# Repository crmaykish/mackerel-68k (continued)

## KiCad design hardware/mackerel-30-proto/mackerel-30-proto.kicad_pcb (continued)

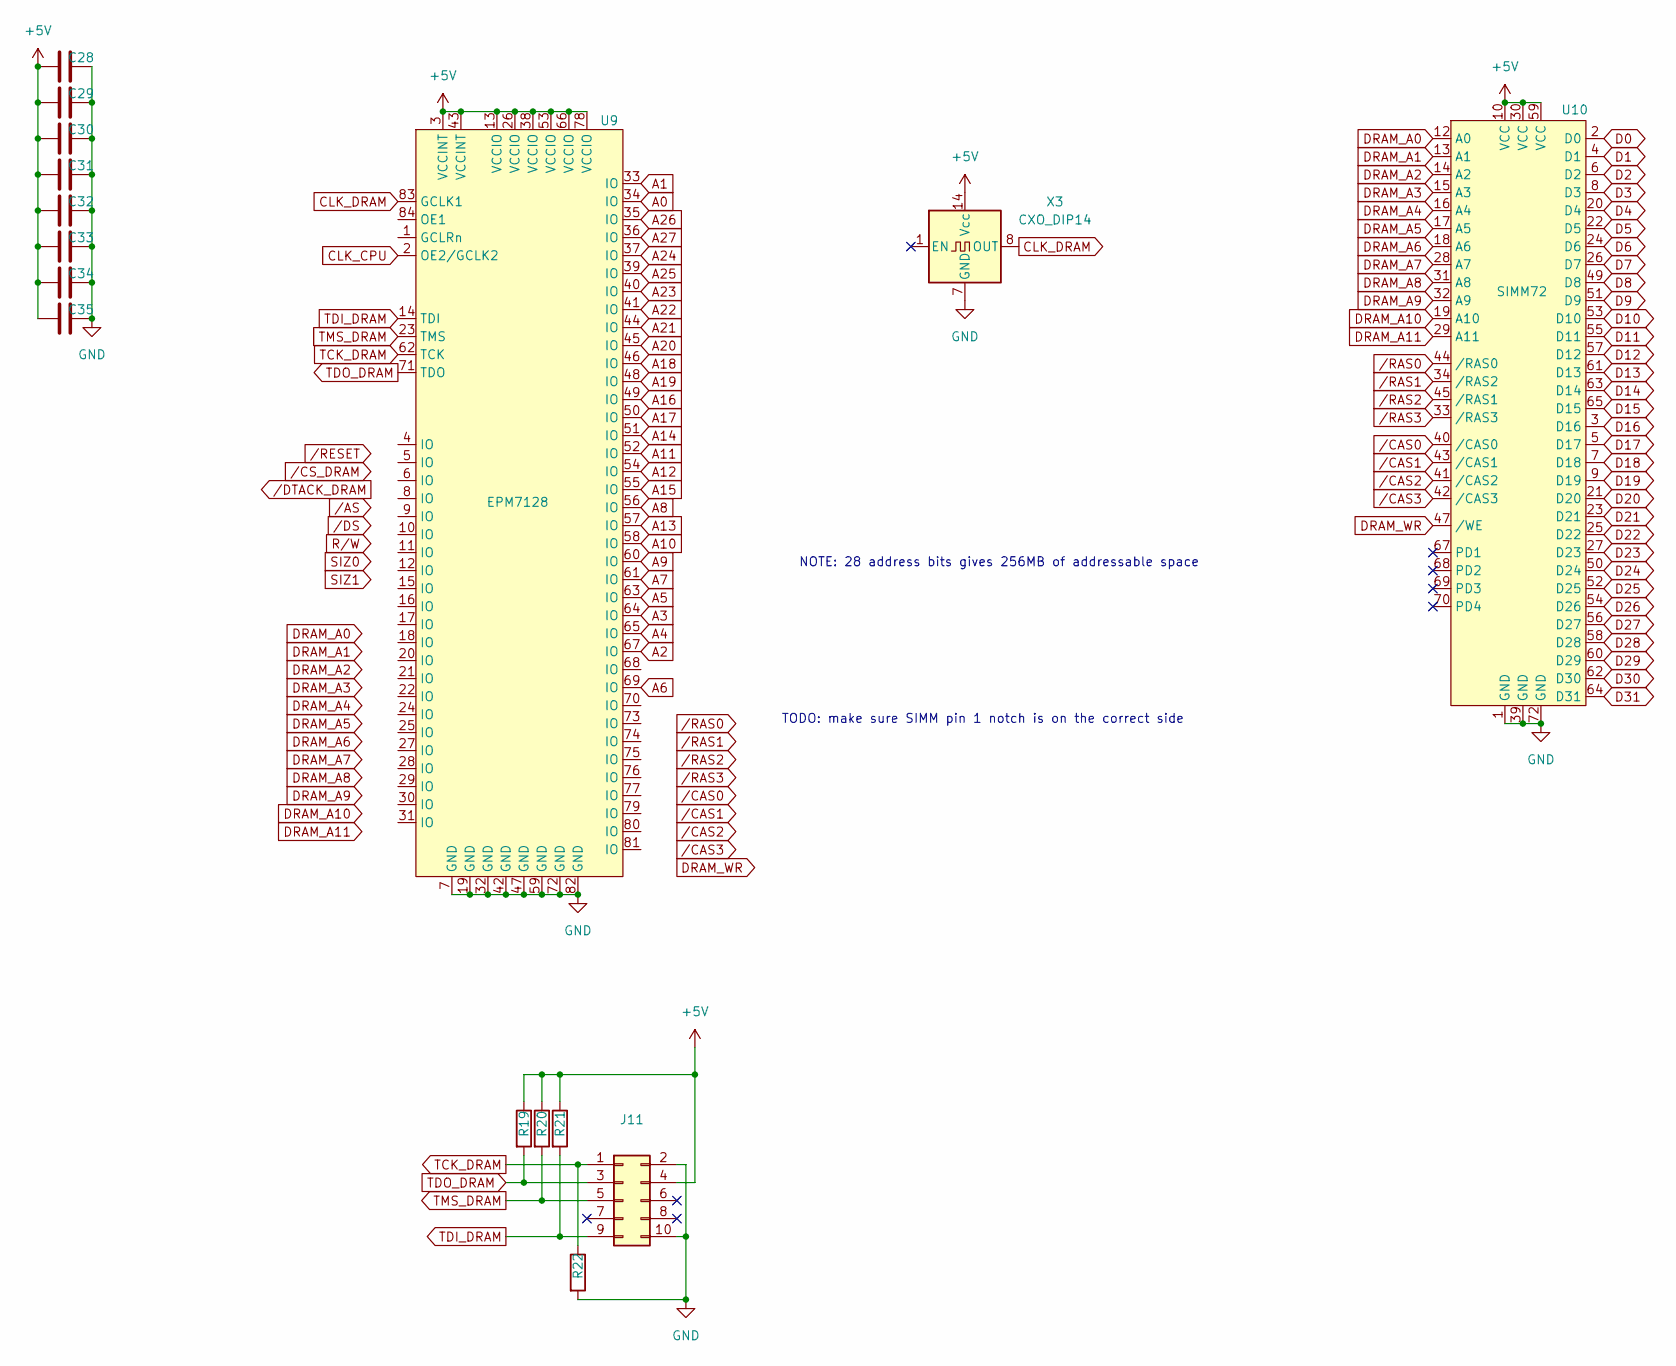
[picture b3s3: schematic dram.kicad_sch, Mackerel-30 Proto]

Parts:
C28, C29, C30, C31, C32, C33, C34, C35: 0.1uF; C_Disc_D4.3mm_W1.9mm_P5.00mm
J11: Conn_02x05_Odd_Even; IDC-Header_2x05_P2.54mm_Vertical
R19, R20, R21, R22: R; R_Axial_DIN0207_L6.3mm_D2.5mm_P7.62mm_Horizontal
U9: EPM7128; PLCC-84_THT-Socket
U10: SIMM72; SIMM-72
X3: CXO_DIP14; Oscillator_DIP-14

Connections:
+5V: C28.1, C29.1, C30.1, C31.1, C32.1, C33.1, C34.1, C35.1, J11.4, R19.1, R20.1, R21.1, U9.3 (VCCINT), U9.13 (VCCIO), U9.26 (VCCIO), U9.38 (VCCIO), U9.43 (VCCINT), U9.53 (VCCIO), U9.66 (VCCIO), U9.78 (VCCIO), U10.10 (VCC), U10.30 (VCC), U10.59 (VCC), X3.14 (Vcc); also elsewhere on the board
A0: U9.34 (IO); also elsewhere on the board
A1: U9.33 (IO); also elsewhere on the board
A2: U9.67 (IO); also elsewhere on the board
A3: U9.64 (IO); also elsewhere on the board
A4: U9.65 (IO); also elsewhere on the board
A5: U9.63 (IO); also elsewhere on the board
A6: U9.69 (IO); also elsewhere on the board
A7: U9.61 (IO); also elsewhere on the board
A8: U9.56 (IO); also elsewhere on the board
A9: U9.60 (IO); also elsewhere on the board
A10: U9.58 (IO); also elsewhere on the board
A11: U9.52 (IO); also elsewhere on the board
A12: U9.54 (IO); also elsewhere on the board
A13: U9.57 (IO); also elsewhere on the board
A14: U9.51 (IO); also elsewhere on the board
A15: U9.55 (IO); also elsewhere on the board
A16: U9.49 (IO); also elsewhere on the board
A17: U9.50 (IO); also elsewhere on the board
A18: U9.46 (IO); also elsewhere on the board
A19: U9.48 (IO); also elsewhere on the board
A20: U9.45 (IO); also elsewhere on the board
A21: U9.44 (IO); also elsewhere on the board
A22: U9.41 (IO); also elsewhere on the board
A23: U9.40 (IO); also elsewhere on the board
A24: U9.37 (IO); also elsewhere on the board
A25: U9.39 (IO); also elsewhere on the board
A26: U9.35 (IO); also elsewhere on the board
A27: U9.36 (IO); also elsewhere on the board
CLK_CPU: U9.2 (OE2/GCLK2); also elsewhere on the board
CLK_DRAM: U9.83 (GCLK1), X3.8 (OUT)
D0: U10.2 (D0); also elsewhere on the board
D1: U10.4 (D1); also elsewhere on the board
D2: U10.6 (D2); also elsewhere on the board
D3: U10.8 (D3); also elsewhere on the board
D4: U10.20 (D4); also elsewhere on the board
D5: U10.22 (D5); also elsewhere on the board
D6: U10.24 (D6); also elsewhere on the board
D7: U10.26 (D7); also elsewhere on the board
D8: U10.49 (D8); also elsewhere on the board
D9: U10.51 (D9); also elsewhere on the board
D10: U10.53 (D10); also elsewhere on the board
D11: U10.55 (D11); also elsewhere on the board
D12: U10.57 (D12); also elsewhere on the board
D13: U10.61 (D13); also elsewhere on the board
D14: U10.63 (D14); also elsewhere on the board
D15: U10.65 (D15); also elsewhere on the board
D16: U10.3 (D16); also elsewhere on the board
D17: U10.5 (D17); also elsewhere on the board
D18: U10.7 (D18); also elsewhere on the board
D19: U10.9 (D19); also elsewhere on the board
D20: U10.21 (D20); also elsewhere on the board
D21: U10.23 (D21); also elsewhere on the board
D22: U10.25 (D22); also elsewhere on the board
D23: U10.27 (D23); also elsewhere on the board
D24: U10.50 (D24); also elsewhere on the board
D25: U10.52 (D25); also elsewhere on the board
D26: U10.54 (D26); also elsewhere on the board
D27: U10.56 (D27); also elsewhere on the board
D28: U10.58 (D28); also elsewhere on the board
D29: U10.60 (D29); also elsewhere on the board
D30: U10.62 (D30); also elsewhere on the board
D31: U10.64 (D31); also elsewhere on the board
DRAM_A0: U10.12 (A0)
DRAM_A1: U10.13 (A1)
DRAM_A2: U10.14 (A2)
DRAM_A3: U10.15 (A3)
DRAM_A4: U10.16 (A4)
DRAM_A5: U10.17 (A5)
DRAM_A6: U10.18 (A6)
DRAM_A7: U10.28 (A7)
DRAM_A8: U10.31 (A8)
DRAM_A9: U10.32 (A9)
DRAM_A10: U10.19 (A10)
DRAM_A11: U10.29 (A11)
DRAM_WR: U10.47 (/WE)
GND: C28.2, C29.2, C30.2, C31.2, C32.2, C33.2, C34.2, C35.2, J11.2, J11.10, R22.2, U9.7 (GND), U9.19 (GND), U9.32 (GND), U9.42 (GND), U9.47 (GND), U9.59 (GND), U9.72 (GND), U9.82 (GND), U10.1 (GND), U10.39 (GND), U10.72 (GND), X3.7 (GND); also elsewhere on the board
TCK_DRAM: J11.1, R22.1, U9.62 (TCK)
TDI_DRAM: J11.9, R21.2, U9.14 (TDI)
TDO_DRAM: J11.3, R19.2, U9.71 (TDO)
TMS_DRAM: J11.5, R20.2, U9.23 (TMS)
/CAS0: U10.40 (/CAS0)
/CAS1: U10.43 (/CAS1)
/CAS2: U10.41 (/CAS2)
/CAS3: U10.42 (/CAS3)
/RAS0: U10.44 (/RAS0)
/RAS1: U10.34 (/RAS2)
/RAS2: U10.45 (/RAS1)
/RAS3: U10.33 (/RAS3)

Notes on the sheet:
NOTE: 28 address bits gives 256MB of addressable space
TODO: make sure SIMM pin 1 notch is on the correct side

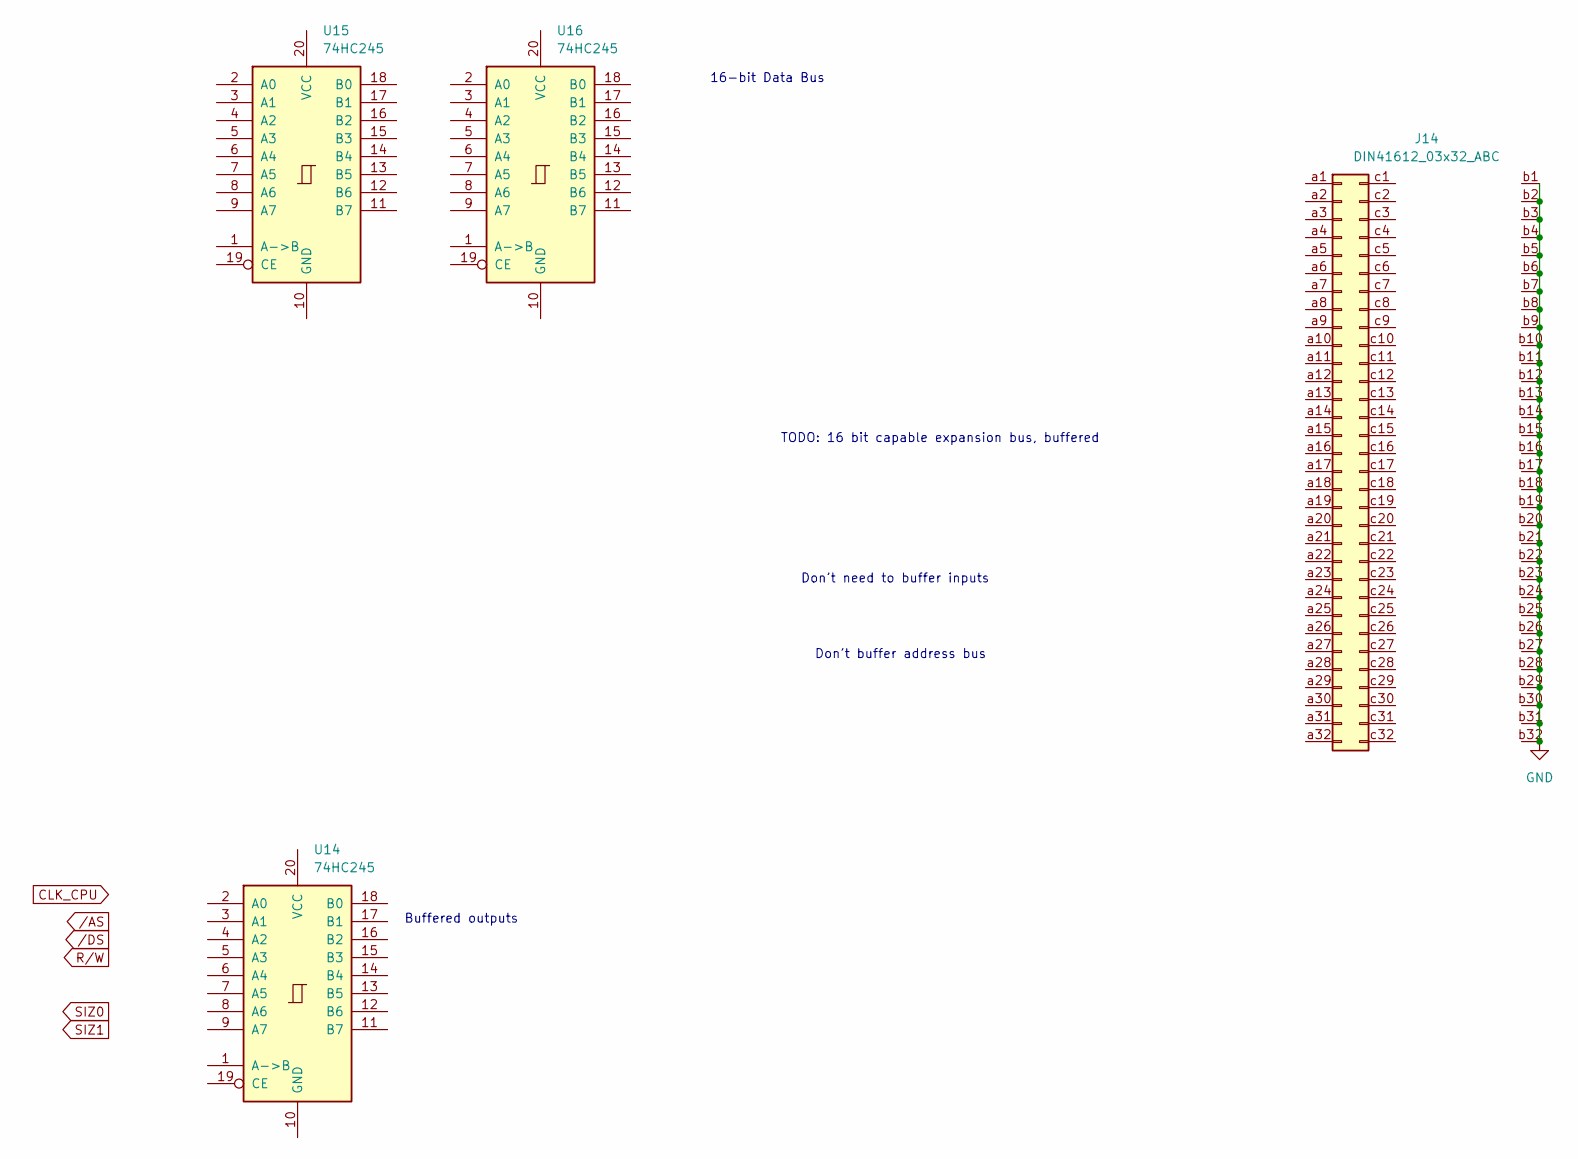
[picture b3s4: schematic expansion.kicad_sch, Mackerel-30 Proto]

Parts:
J14: DIN41612_03x32_ABC; DIN41612_C_3x32_Female_Vertical_THT
U14, U15, U16: 74HC245; DIP-20_W7.62mm_Socket

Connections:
GND: J14.b1, J14.b2, J14.b3, J14.b4, J14.b5, J14.b6, J14.b7, J14.b8, J14.b9, J14.b10, J14.b11, J14.b12, J14.b13, J14.b14, J14.b15, J14.b16, J14.b17, J14.b18, J14.b19, J14.b20, J14.b21, J14.b22, J14.b23, J14.b24, J14.b25, J14.b26, J14.b27, J14.b28, J14.b29, J14.b30, J14.b31, J14.b32; also elsewhere on the board

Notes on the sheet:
16-bit Data Bus
Don't buffer address bus
Buffered outputs
TODO: 16 bit capable expansion bus, buffered
Don't need to buffer inputs

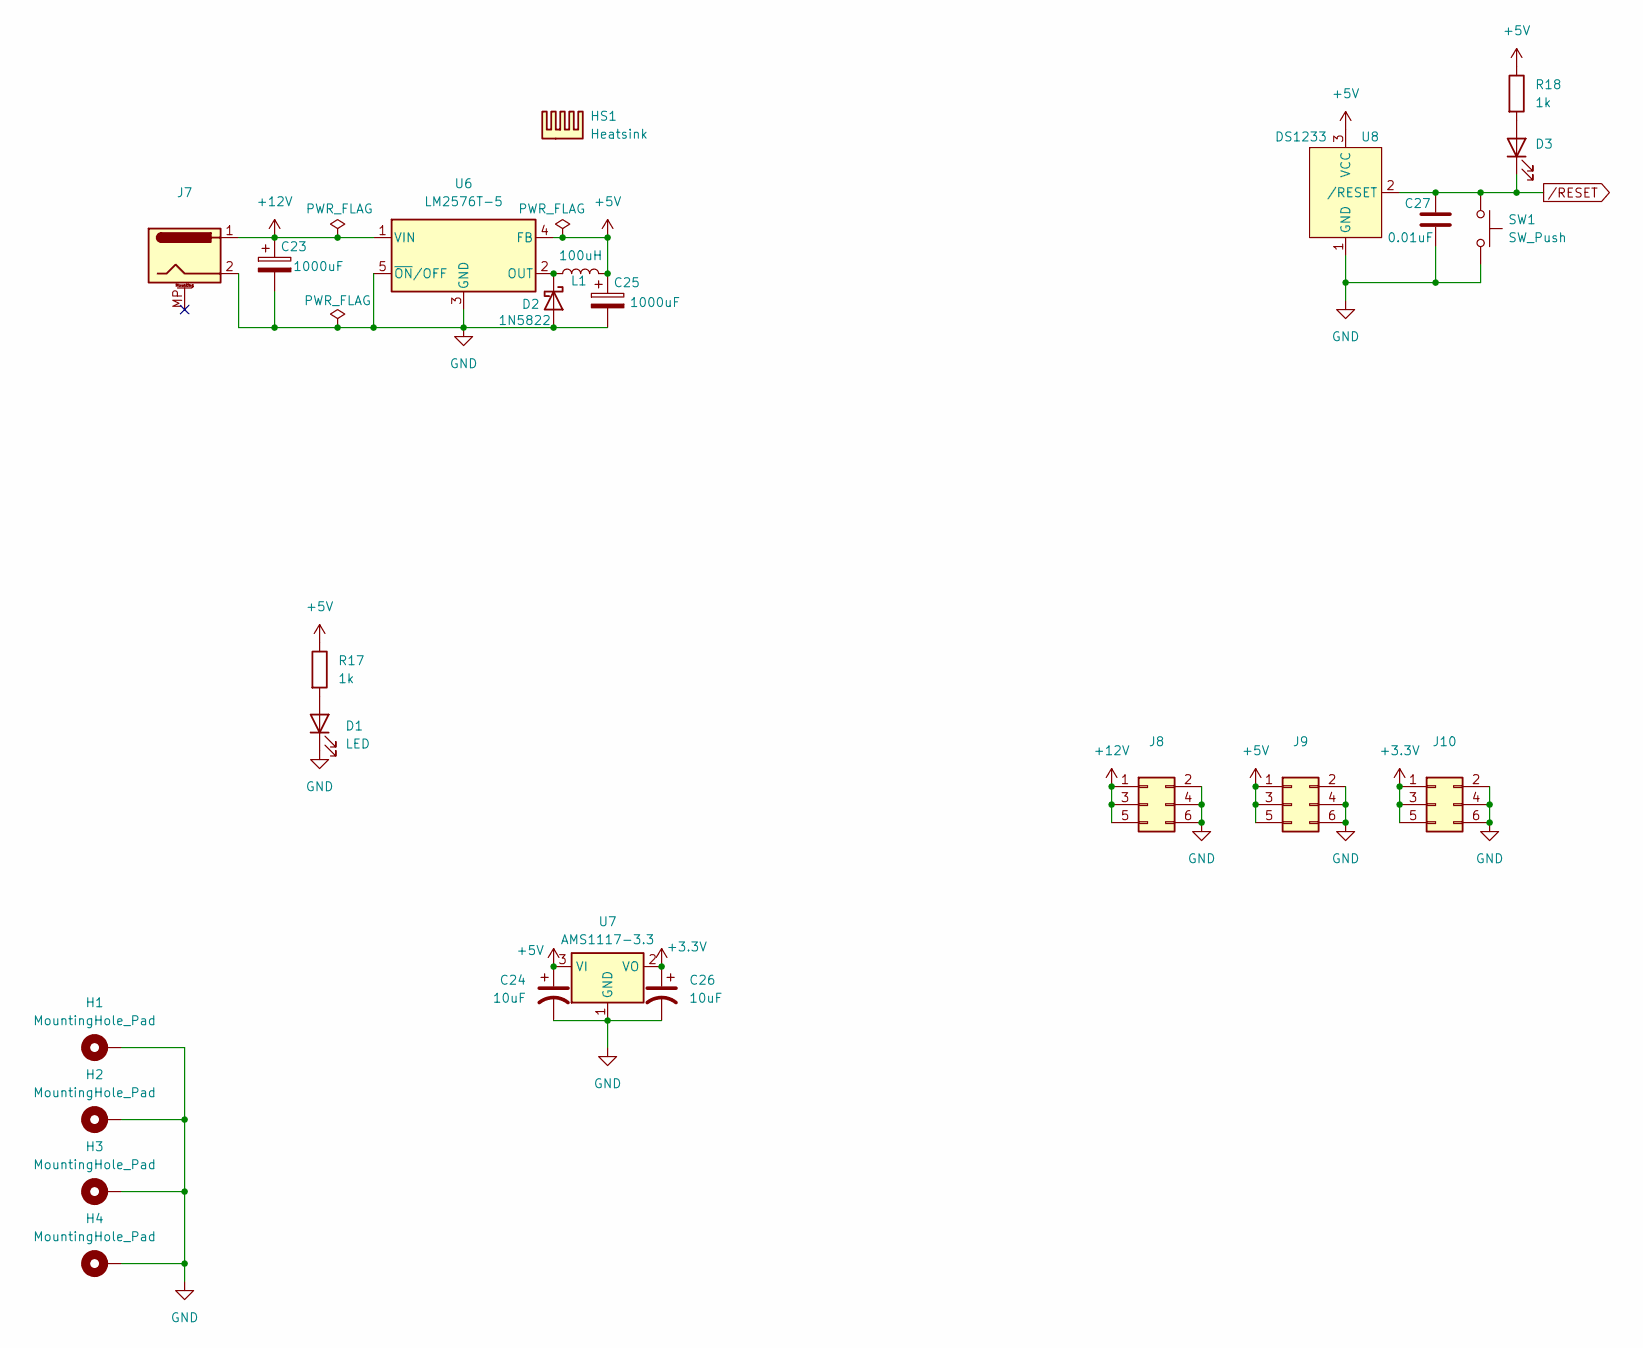
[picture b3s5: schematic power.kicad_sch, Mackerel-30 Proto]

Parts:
C23, C25: 1000uF; CP_Radial_D10.0mm_P5.00mm
C24, C26: 10uF; CP_Radial_D5.0mm_P2.00mm
C27: 0.01uF; C_Disc_D4.3mm_W1.9mm_P5.00mm
D1, D3: LED; LED_D5.0mm
D2: 1N5822; D_DO-27_P15.24mm_Horizontal
H1, H2, H3, H4: MountingHole_Pad; MountingHole_3.2mm_M3_Pad_Via
HS1: Heatsink; Heatsink_Stonecold_HS-S02_13.21x9.53mm
J7: Barrel_Jack_MountingPin; BarrelJack_Horizontal
J8, J9, J10: Conn_02x03_Odd_Even; PinHeader_2x03_P2.54mm_Vertical
L1: 100uH; L_Radial_D10.0mm_P5.00mm_Fastron_07M
R17, R18: 1k; R_Axial_DIN0207_L6.3mm_D2.5mm_P7.62mm_Horizontal
SW1: SW_Push; SW_PUSH_6mm_H5mm
U6: LM2576T-5; TO-220-5_Vertical
U7: AMS1117-3.3; SOT-223-3_TabPin2
U8: DS1233; TO-92

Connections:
+3.3V: C26.1, J10.1, J10.3, J10.5, U7.2 (VO); also elsewhere on the board
+5V: C24.1, C25.1, J9.1, J9.3, J9.5, L1.2, R17.1, R18.1, U6.4 (FB), U7.3 (VI), U8.3 (VCC); also elsewhere on the board
+12V: C23.1, J7.1, J8.1, J8.3, J8.5, U6.1 (VIN); also elsewhere on the board
GND: C23.2, C24.2, C25.2, C26.2, C27.2, D1.1 (K), D2.2 (A), H1.1, H2.1, H3.1, H4.1, J7.2, J8.2, J8.4, J8.6, J9.2, J9.4, J9.6, J10.2, J10.4, J10.6, SW1.2, U6.3 (GND), U6.5 (~ON/OFF), U7.1 (GND), U8.1 (GND); also elsewhere on the board
unnamed: D1.2 (A), R17.2
unnamed: D2.1 (K), L1.1, U6.2 (OUT)
unnamed: D3.2 (A), R18.2
/RESET: C27.1, D3.1 (K), SW1.1, U8.2 (/RESET); also elsewhere on the board

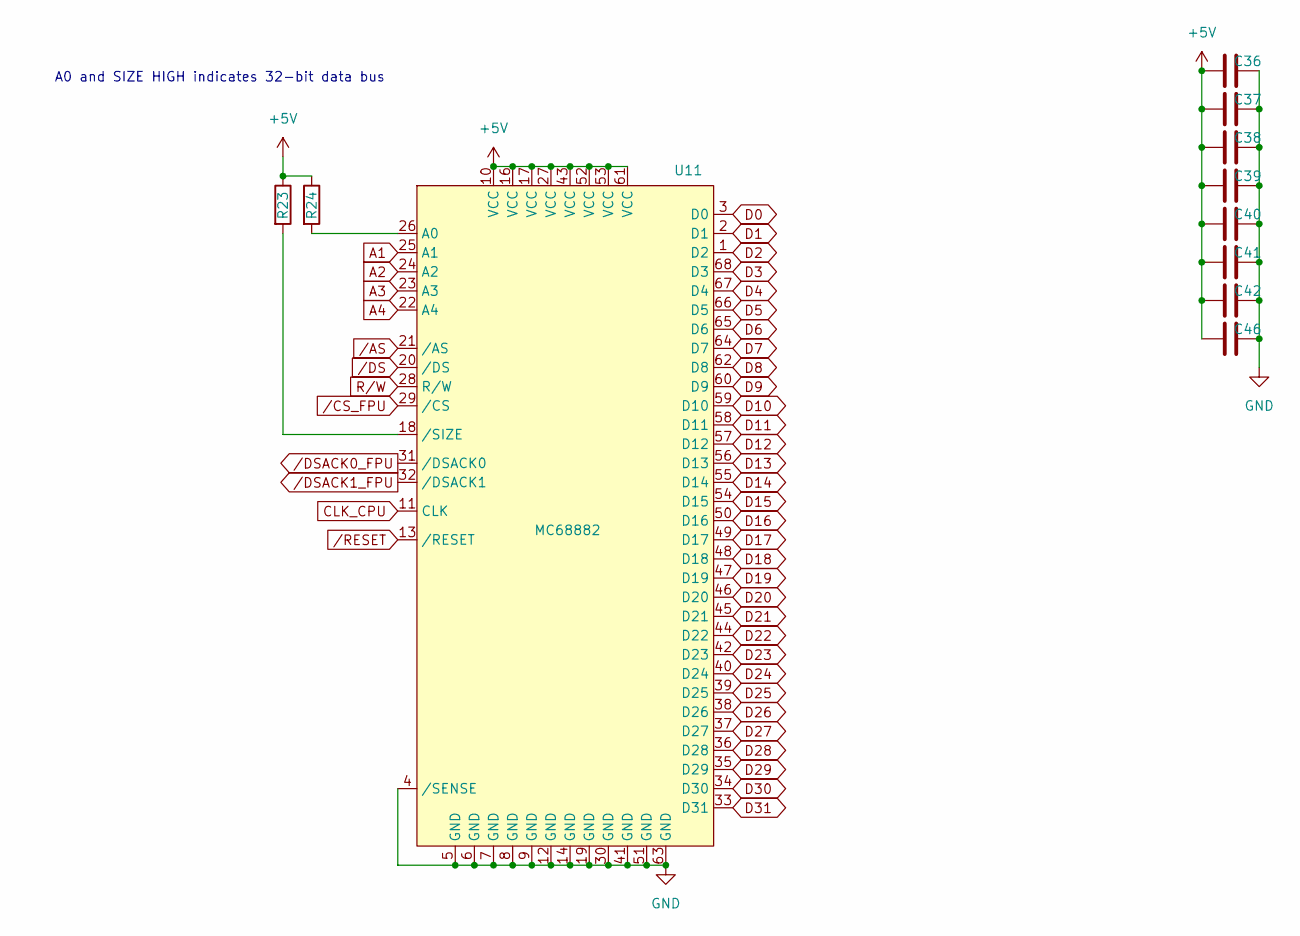
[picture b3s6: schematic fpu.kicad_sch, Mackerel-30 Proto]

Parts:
C36, C37, C38, C39, C40, C41, C42, C46: 0.1uF; C_Disc_D4.3mm_W1.9mm_P5.00mm
R23, R24: 4k7; R_Axial_DIN0207_L6.3mm_D2.5mm_P7.62mm_Horizontal
U11: MC68882; PLCC-68_THT-Socket

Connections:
+5V: C36.1, C37.1, C38.1, C39.1, C40.1, C41.1, C42.1, C46.1, R23.1, R24.1, U11.10 (VCC), U11.16 (VCC), U11.17 (VCC), U11.27 (VCC), U11.43 (VCC), U11.52 (VCC), U11.53 (VCC), U11.61 (VCC); also elsewhere on the board
A1: U11.25 (A1); also elsewhere on the board
A2: U11.24 (A2); also elsewhere on the board
A3: U11.23 (A3); also elsewhere on the board
A4: U11.22 (A4); also elsewhere on the board
CLK_CPU: U11.11 (CLK); also elsewhere on the board
D0: U11.3 (D0); also elsewhere on the board
D1: U11.2 (D1); also elsewhere on the board
D2: U11.1 (D2); also elsewhere on the board
D3: U11.68 (D3); also elsewhere on the board
D4: U11.67 (D4); also elsewhere on the board
D5: U11.66 (D5); also elsewhere on the board
D6: U11.65 (D6); also elsewhere on the board
D7: U11.64 (D7); also elsewhere on the board
D8: U11.62 (D8); also elsewhere on the board
D9: U11.60 (D9); also elsewhere on the board
D10: U11.59 (D10); also elsewhere on the board
D11: U11.58 (D11); also elsewhere on the board
D12: U11.57 (D12); also elsewhere on the board
D13: U11.56 (D13); also elsewhere on the board
D14: U11.55 (D14); also elsewhere on the board
D15: U11.54 (D15); also elsewhere on the board
D16: U11.50 (D16); also elsewhere on the board
D17: U11.49 (D17); also elsewhere on the board
D18: U11.48 (D18); also elsewhere on the board
D19: U11.47 (D19); also elsewhere on the board
D20: U11.46 (D20); also elsewhere on the board
D21: U11.45 (D21); also elsewhere on the board
D22: U11.44 (D22); also elsewhere on the board
D23: U11.42 (D23); also elsewhere on the board
D24: U11.40 (D24); also elsewhere on the board
D25: U11.39 (D25); also elsewhere on the board
D26: U11.38 (D26); also elsewhere on the board
D27: U11.37 (D27); also elsewhere on the board
D28: U11.36 (D28); also elsewhere on the board
D29: U11.35 (D29); also elsewhere on the board
D30: U11.34 (D30); also elsewhere on the board
D31: U11.33 (D31); also elsewhere on the board
GND: C36.2, C37.2, C38.2, C39.2, C40.2, C41.2, C42.2, C46.2, U11.4 (/SENSE), U11.5 (GND), U11.6 (GND), U11.7 (GND), U11.8 (GND), U11.9 (GND), U11.12 (GND), U11.14 (GND), U11.19 (GND), U11.30 (GND), U11.41 (GND), U11.51 (GND), U11.63 (GND); also elsewhere on the board
unnamed: R24.2, U11.26 (A0)
unnamed: R23.2, U11.18 (/SIZE)
R/W: U11.28 (R/W); also elsewhere on the board
/AS: U11.21 (/AS); also elsewhere on the board
/CS_FPU: U11.29 (/CS); also elsewhere on the board
/DS: U11.20 (/DS); also elsewhere on the board
/DSACK0_FPU: U11.31 (/DSACK0); also elsewhere on the board
/DSACK1_FPU: U11.32 (/DSACK1); also elsewhere on the board
/RESET: U11.13 (/RESET); also elsewhere on the board

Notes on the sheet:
A0 and SIZE HIGH indicates 32-bit data bus

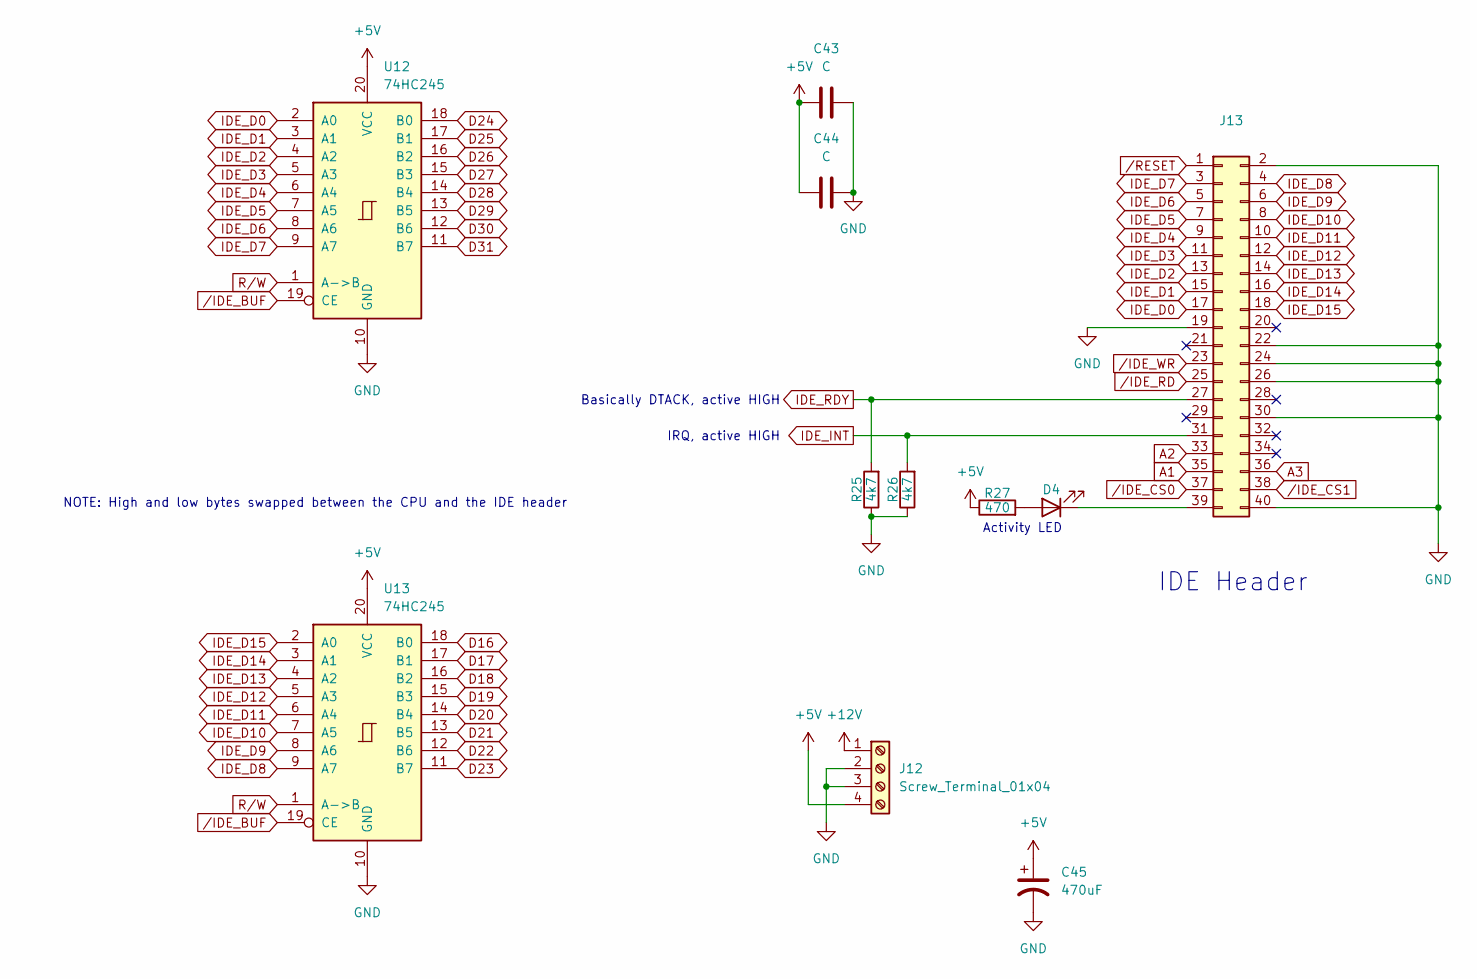
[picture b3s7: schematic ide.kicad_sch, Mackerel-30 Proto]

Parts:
C43, C44: C; C_Disc_D4.3mm_W1.9mm_P5.00mm
C45: 470uF; CP_Radial_D8.0mm_P3.50mm
D4: LED; LED_D5.0mm
J12: Screw_Terminal_01x04; TerminalBlock_bornier-4_P5.08mm
J13: Conn_02x20_Odd_Even; IDC-Header_2x20_P2.54mm_Vertical
R25, R26: 4k7; R_Axial_DIN0207_L6.3mm_D2.5mm_P7.62mm_Horizontal
R27: 470; R_Axial_DIN0207_L6.3mm_D2.5mm_P7.62mm_Horizontal
U12, U13: 74HC245; DIP-20_W7.62mm_Socket

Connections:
+5V: C43.1, C44.1, C45.1, J12.4, R27.1, U12.20 (VCC), U13.20 (VCC); also elsewhere on the board
+12V: J12.1; also elsewhere on the board
A1: J13.35; also elsewhere on the board
A2: J13.33; also elsewhere on the board
A3: J13.36; also elsewhere on the board
D16: U13.18 (B0); also elsewhere on the board
D17: U13.17 (B1); also elsewhere on the board
D18: U13.16 (B2); also elsewhere on the board
D19: U13.15 (B3); also elsewhere on the board
D20: U13.14 (B4); also elsewhere on the board
D21: U13.13 (B5); also elsewhere on the board
D22: U13.12 (B6); also elsewhere on the board
D23: U13.11 (B7); also elsewhere on the board
D24: U12.18 (B0); also elsewhere on the board
D25: U12.17 (B1); also elsewhere on the board
D26: U12.16 (B2); also elsewhere on the board
D27: U12.15 (B3); also elsewhere on the board
D28: U12.14 (B4); also elsewhere on the board
D29: U12.13 (B5); also elsewhere on the board
D30: U12.12 (B6); also elsewhere on the board
D31: U12.11 (B7); also elsewhere on the board
GND: C43.2, C44.2, C45.2, J12.2, J12.3, J13.2, J13.19, J13.22, J13.24, J13.26, J13.30, J13.40, R25.1, R26.1, U12.10 (GND), U13.10 (GND); also elsewhere on the board
IDE_D0: J13.17, U12.2 (A0)
IDE_D1: J13.15, U12.3 (A1)
IDE_D2: J13.13, U12.4 (A2)
IDE_D3: J13.11, U12.5 (A3)
IDE_D4: J13.9, U12.6 (A4)
IDE_D5: J13.7, U12.7 (A5)
IDE_D6: J13.5, U12.8 (A6)
IDE_D7: J13.3, U12.9 (A7)
IDE_D8: J13.4, U13.9 (A7)
IDE_D9: J13.6, U13.8 (A6)
IDE_D10: J13.8, U13.7 (A5)
IDE_D11: J13.10, U13.6 (A4)
IDE_D12: J13.12, U13.5 (A3)
IDE_D13: J13.14, U13.4 (A2)
IDE_D14: J13.16, U13.3 (A1)
IDE_D15: J13.18, U13.2 (A0)
IDE_INT: J13.31, R26.2; also elsewhere on the board
IDE_RDY: J13.27, R25.2; also elsewhere on the board
unnamed: D4.2 (A), R27.2
unnamed: D4.1 (K), J13.39
R/W: U12.1 (A->B), U13.1 (A->B); also elsewhere on the board
/IDE_BUF: U12.19 (CE), U13.19 (CE); also elsewhere on the board
/IDE_CS0: J13.37; also elsewhere on the board
/IDE_CS1: J13.38; also elsewhere on the board
/IDE_RD: J13.25; also elsewhere on the board
/IDE_WR: J13.23; also elsewhere on the board
/RESET: J13.1; also elsewhere on the board

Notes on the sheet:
Activity LED
IRQ, active HIGH
NOTE: High and low bytes swapped between the CPU and the IDE header
Basically DTACK, active HIGH
IDE Header

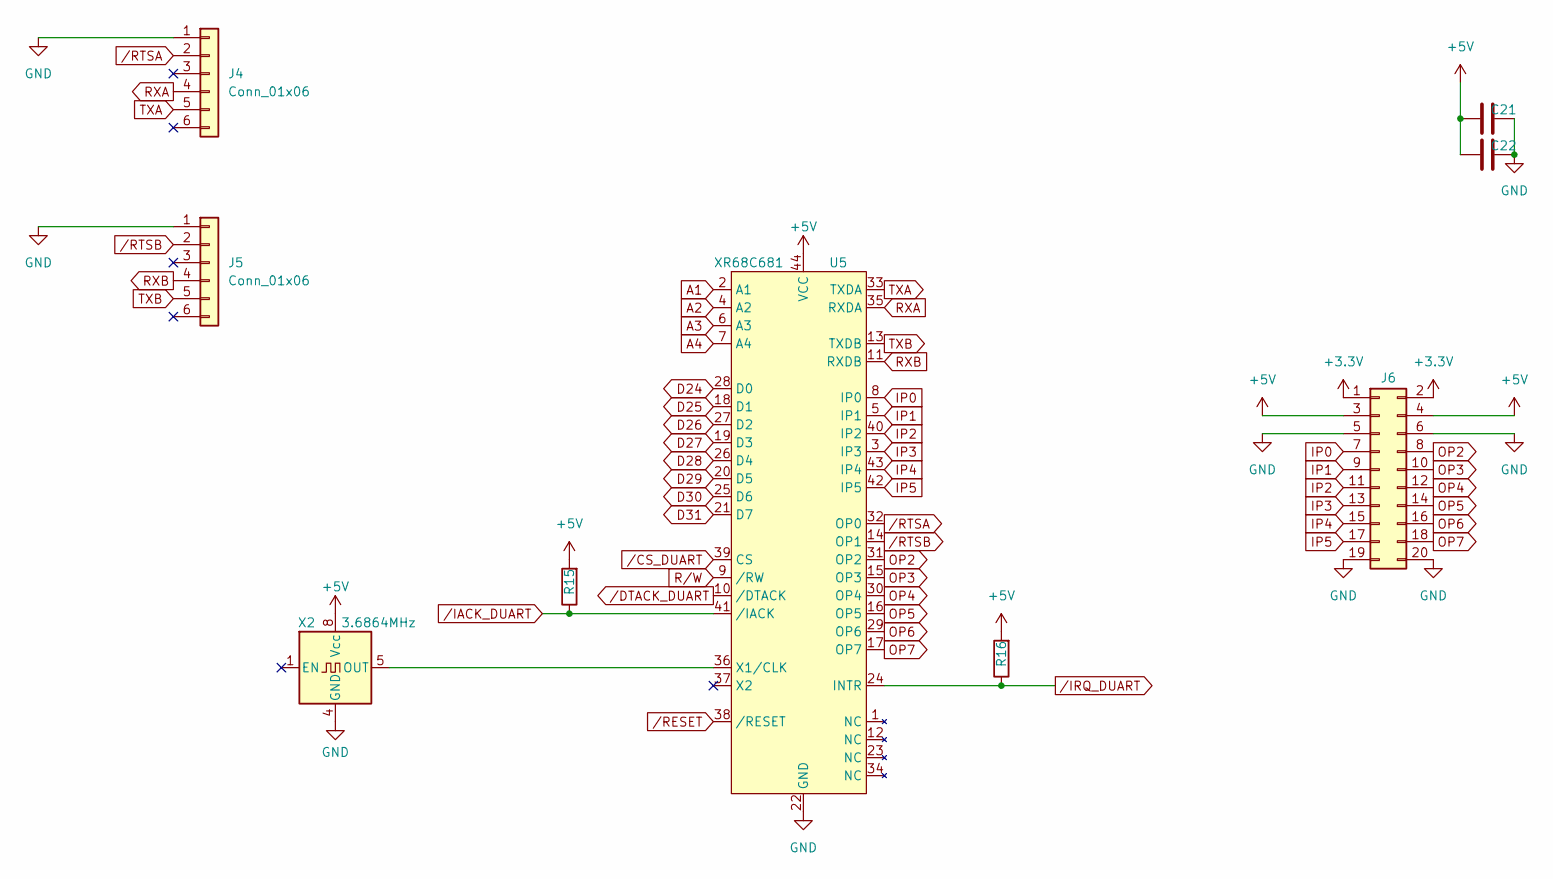
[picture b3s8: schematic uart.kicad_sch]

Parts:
C21, C22: 0.1uF; C_Disc_D4.3mm_W1.9mm_P5.00mm
J4, J5: Conn_01x06; PinHeader_1x06_P2.54mm_Vertical
J6: Conn_02x10_Odd_Even; PinHeader_2x10_P2.54mm_Vertical
R15, R16: R; R_Axial_DIN0207_L6.3mm_D2.5mm_P7.62mm_Horizontal
U5: XR68C681; PLCC-44_THT-Socket
X2: 3.6864MHz; Oscillator_DIP-8

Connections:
+3.3V: J6.1, J6.2; also elsewhere on the board
+5V: C21.1, C22.1, J6.3, J6.4, R15.2, R16.2, U5.44 (VCC), X2.8 (Vcc); also elsewhere on the board
A1: U5.2 (A1); also elsewhere on the board
A2: U5.4 (A2); also elsewhere on the board
A3: U5.6 (A3); also elsewhere on the board
A4: U5.7 (A4); also elsewhere on the board
D24: U5.28 (D0); also elsewhere on the board
D25: U5.18 (D1); also elsewhere on the board
D26: U5.27 (D2); also elsewhere on the board
D27: U5.19 (D3); also elsewhere on the board
D28: U5.26 (D4); also elsewhere on the board
D29: U5.20 (D5); also elsewhere on the board
D30: U5.25 (D6); also elsewhere on the board
D31: U5.21 (D7); also elsewhere on the board
GND: C21.2, C22.2, J4.1, J5.1, J6.5, J6.6, J6.19, J6.20, U5.22 (GND), X2.4 (GND); also elsewhere on the board
IP0: J6.7, U5.8 (IP0)
IP1: J6.9, U5.5 (IP1)
IP2: J6.11, U5.40 (IP2)
IP3: J6.13, U5.3 (IP3)
IP4: J6.15, U5.43 (IP4)
IP5: J6.17, U5.42 (IP5)
unnamed: U5.36 (X1/CLK), X2.5 (OUT)
OP2: J6.8, U5.31 (OP2)
OP3: J6.10, U5.15 (OP3)
OP4: J6.12, U5.30 (OP4)
OP5: J6.14, U5.16 (OP5)
OP6: J6.16, U5.29 (OP6)
OP7: J6.18, U5.17 (OP7)
RXA: J4.4, U5.35 (RXDA)
RXB: J5.4, U5.11 (RXDB)
R/W: U5.9 (/RW); also elsewhere on the board
TXA: J4.5, U5.33 (TXDA)
TXB: J5.5, U5.13 (TXDB)
/CS_DUART: U5.39 (CS); also elsewhere on the board
/DTACK_DUART: U5.10 (/DTACK); also elsewhere on the board
/IACK_DUART: R15.1, U5.41 (/IACK); also elsewhere on the board
/IRQ_DUART: R16.1, U5.24 (INTR); also elsewhere on the board
/RESET: U5.38 (/RESET); also elsewhere on the board
/RTSA: J4.2, U5.32 (OP0)
/RTSB: J5.2, U5.14 (OP1)

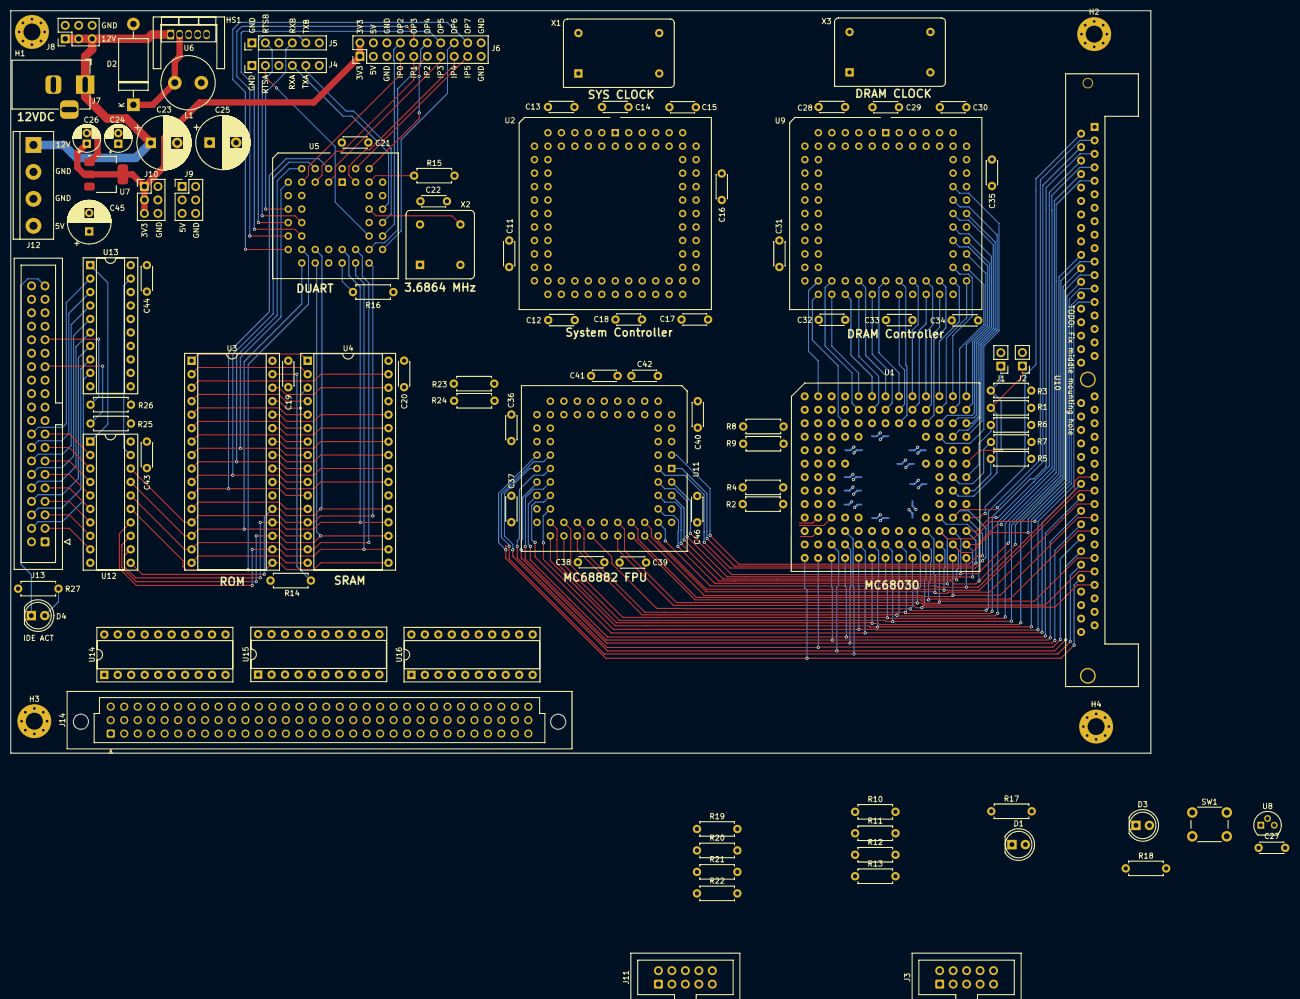
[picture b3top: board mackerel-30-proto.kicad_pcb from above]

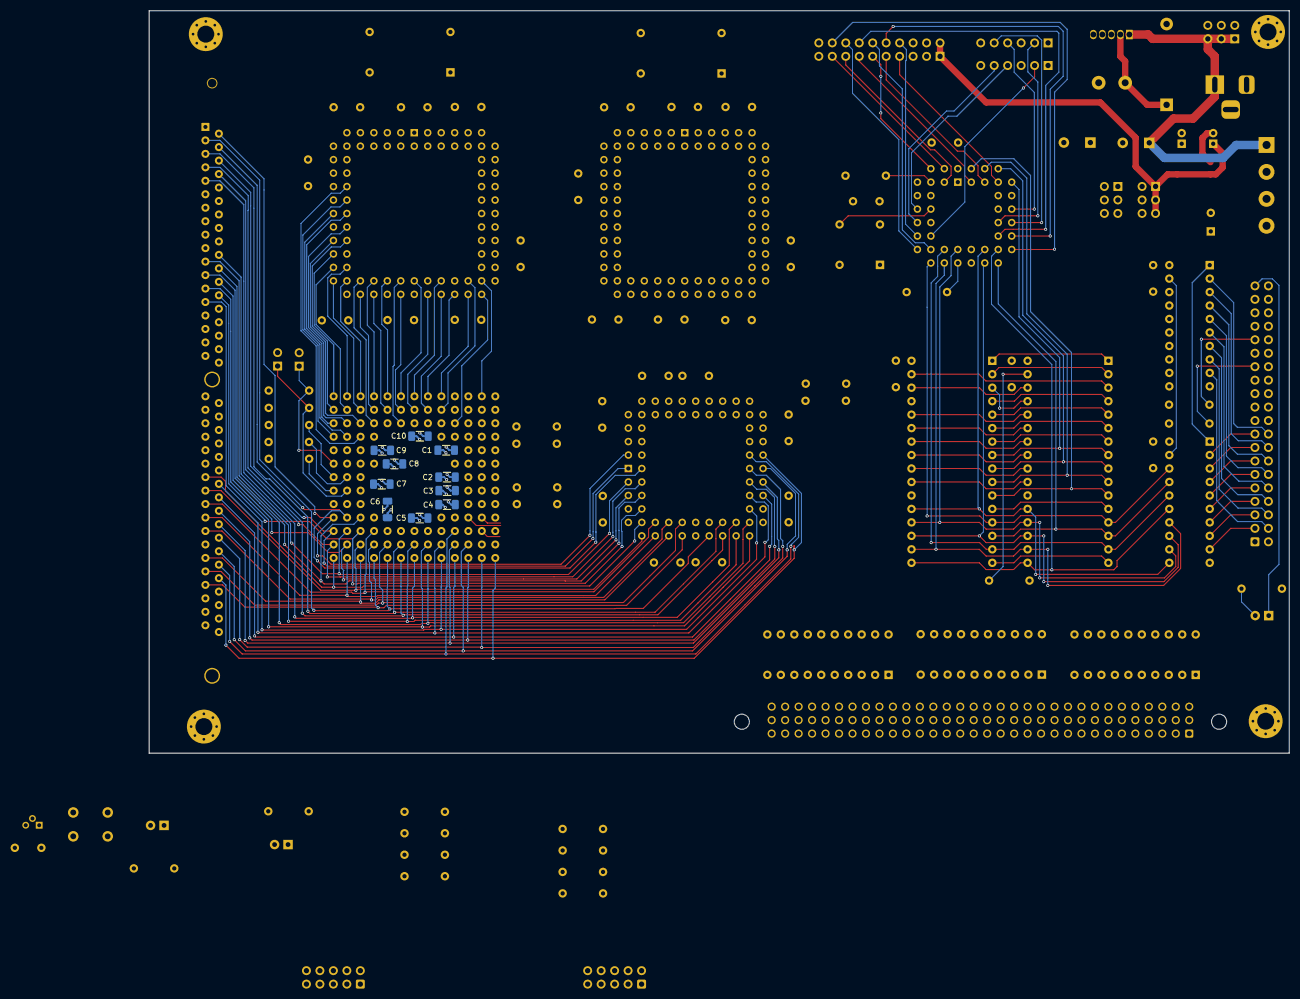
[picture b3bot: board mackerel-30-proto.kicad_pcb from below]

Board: 4 copper layers, 215.0 x 140.0 mm, 117 parts (10 on the bottom side), 160 nets.
